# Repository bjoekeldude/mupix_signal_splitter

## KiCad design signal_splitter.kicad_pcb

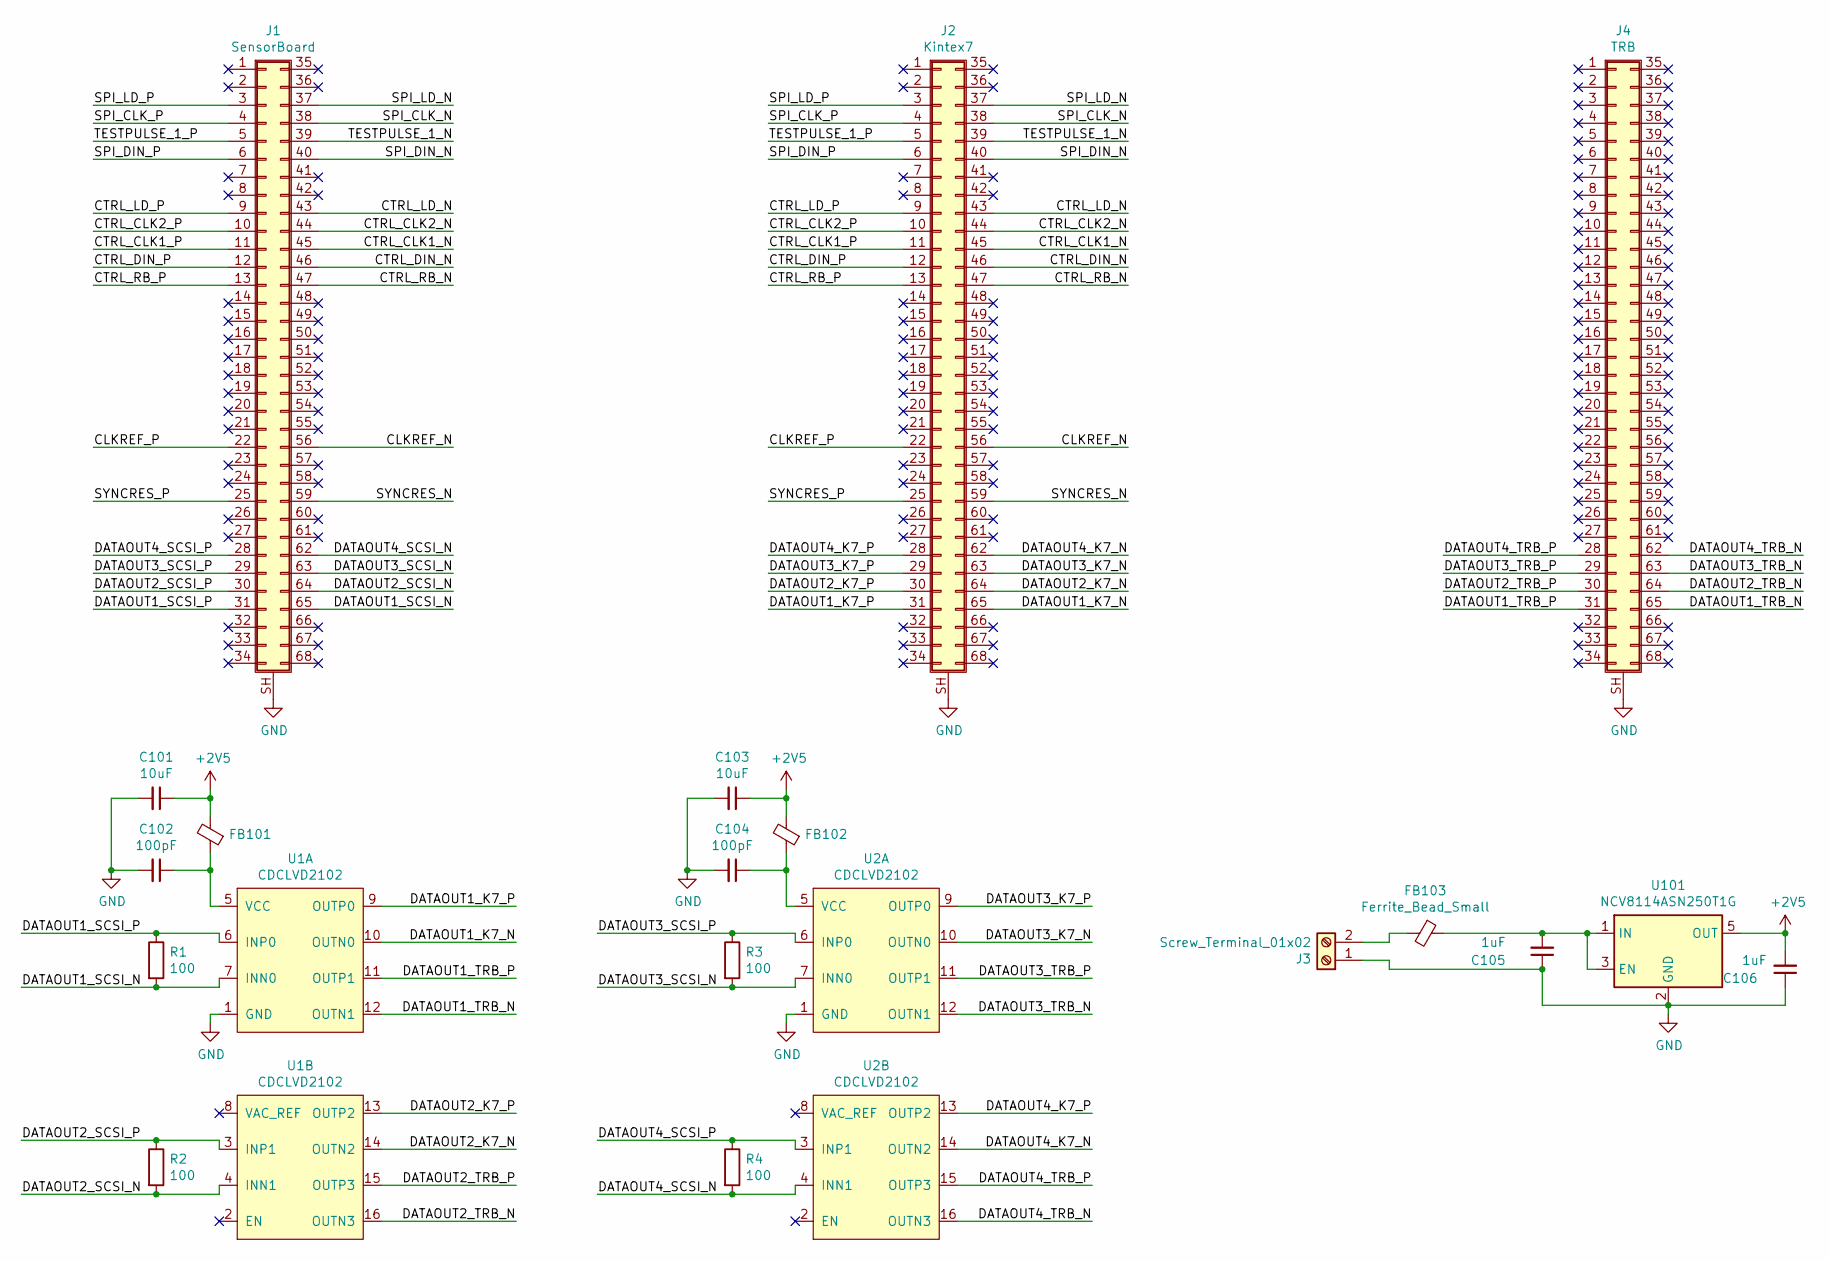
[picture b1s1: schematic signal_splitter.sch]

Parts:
C101, C103: 10uF; C_0402_1005Metric
C102, C104: 100pF; C_0402_1005Metric
C105, C106: 1uF; C_0603_1608Metric
FB101, FB102, FB103: Ferrite_Bead_Small; C_0603_1608Metric
J1: SensorBoard; TE 5749069-7
J2: Kintex7; TE 5749069-7
J3: Screw_Terminal_01x02; TerminalBlock_RND_205-00232_1x02_P5.08mm_Horizontal
J4: TRB; TE 5749069-7
R1, R2, R3, R4: 100; R_0402_1005Metric_Pad0.72x0.64mm_HandSolder
U1, U2: CDCLVD2102; QFN-16-1EP_3x3mm_P0.5mm_EP1.75x1.75mm_ThermalVias; MPN CDCLVD2102RGT
U101: NCV8114ASN250T1G; TSOT-23-5

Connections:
+2V5: C101.1, C103.1, C106.2, FB101.2, FB102.2, U101.5 (OUT)
/CLKREF_N: J1.56, J2.56
/CLKREF_P: J1.22, J2.22
/CTRL_CLK1_N: J1.45, J2.45
/CTRL_CLK1_P: J1.11, J2.11
/CTRL_CLK2_N: J1.44, J2.44
/CTRL_CLK2_P: J1.10, J2.10
/CTRL_DIN_N: J1.46, J2.46
/CTRL_DIN_P: J1.12, J2.12
/CTRL_LD_N: J1.43, J2.43
/CTRL_LD_P: J1.9, J2.9
/CTRL_RB_N: J1.47, J2.47
/CTRL_RB_P: J1.13, J2.13
/DATAOUT1_K7_N: J2.65, U1.10 (OUTN0)
/DATAOUT1_K7_P: J2.31, U1.9 (OUTP0)
/DATAOUT1_SCSI_N: J1.65, R1.2, U1.7 (INN0)
/DATAOUT1_SCSI_P: J1.31, R1.1, U1.6 (INP0)
/DATAOUT1_TRB_N: J4.65, U1.12 (OUTN1)
/DATAOUT1_TRB_P: J4.31, U1.11 (OUTP1)
/DATAOUT2_K7_N: J2.64, U1.14 (OUTN2)
/DATAOUT2_K7_P: J2.30, U1.13 (OUTP2)
/DATAOUT2_SCSI_N: J1.64, R2.2, U1.4 (INN1)
/DATAOUT2_SCSI_P: J1.30, R2.1, U1.3 (INP1)
/DATAOUT2_TRB_N: J4.64, U1.16 (OUTN3)
/DATAOUT2_TRB_P: J4.30, U1.15 (OUTP3)
/DATAOUT3_K7_N: J2.63, U2.10 (OUTN0)
/DATAOUT3_K7_P: J2.29, U2.9 (OUTP0)
/DATAOUT3_SCSI_N: J1.63, R3.2, U2.7 (INN0)
/DATAOUT3_SCSI_P: J1.29, R3.1, U2.6 (INP0)
/DATAOUT3_TRB_N: J4.63, U2.12 (OUTN1)
/DATAOUT3_TRB_P: J4.29, U2.11 (OUTP1)
/DATAOUT4_K7_N: J2.62, U2.14 (OUTN2)
/DATAOUT4_K7_P: J2.28, U2.13 (OUTP2)
/DATAOUT4_SCSI_N: J1.62, R4.2, U2.4 (INN1)
/DATAOUT4_SCSI_P: J1.28, R4.1, U2.3 (INP1)
/DATAOUT4_TRB_N: J4.62, U2.16 (OUTN3)
/DATAOUT4_TRB_P: J4.28, U2.15 (OUTP3)
/SPI_CLK_N: J1.38, J2.38
/SPI_CLK_P: J1.4, J2.4
/SPI_DIN_N: J1.40, J2.40
/SPI_DIN_P: J1.6, J2.6
/SPI_LD_N: J1.37, J2.37
/SPI_LD_P: J1.3, J2.3
/SYNCRES_N: J1.59, J2.59
/SYNCRES_P: J1.25, J2.25
/TESTPULSE_1_N: J1.39, J2.39
/TESTPULSE_1_P: J1.5, J2.5
GND: C101.2, C102.2, C103.2, C104.2, C105.1, C106.1, J1.SH (Shield), J2.SH (Shield), J3.1, J4.SH (Shield), U1.1 (GND), U2.1 (GND), U101.2 (GND)
unnamed: C102.1, FB101.1, U1.5 (VCC)
unnamed: C104.1, FB102.1, U2.5 (VCC)
unnamed: C105.2, FB103.1, U101.1 (IN), U101.3 (EN)
unnamed: FB103.2, J3.2

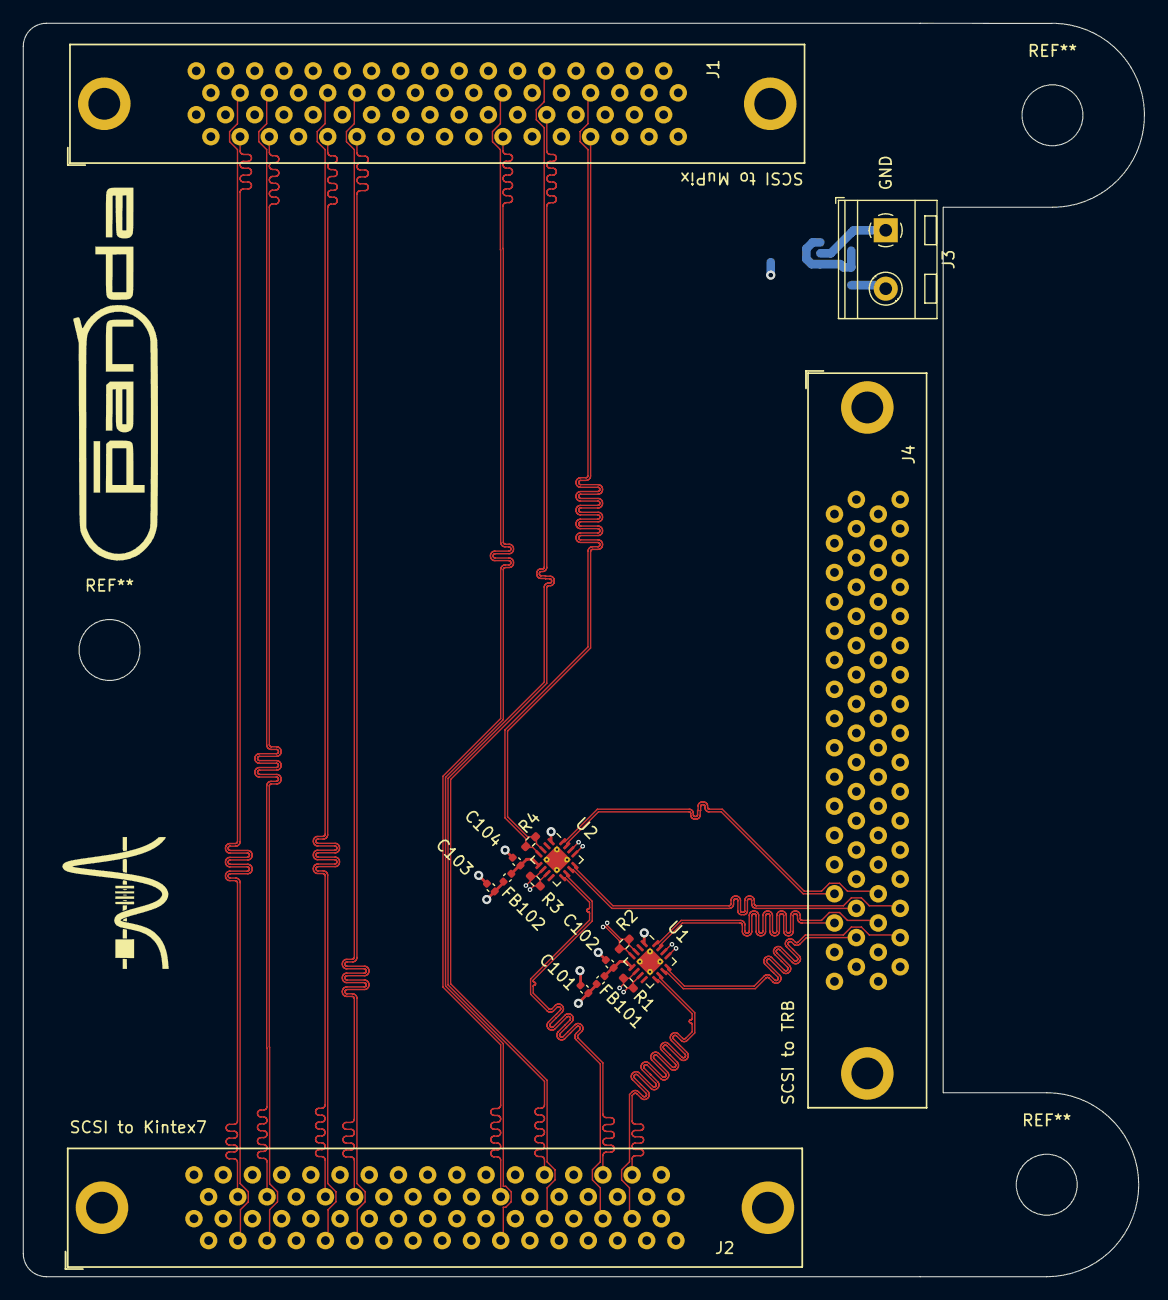
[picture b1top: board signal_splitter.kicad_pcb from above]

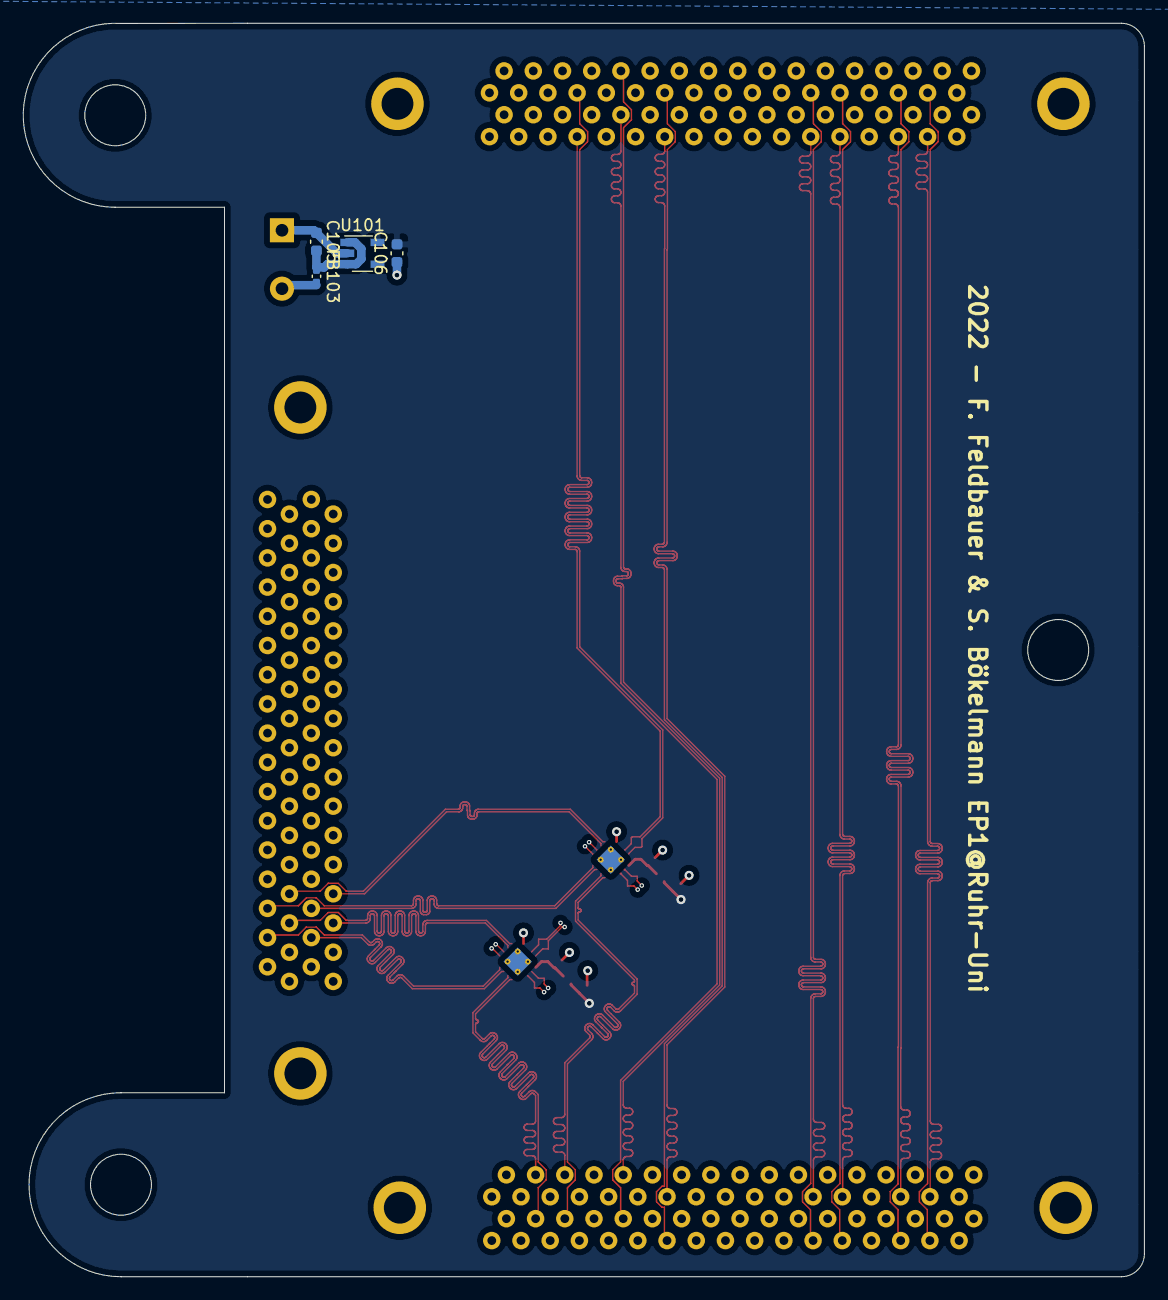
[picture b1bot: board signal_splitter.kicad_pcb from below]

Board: 4 copper layers, 97.5 x 109.0 mm, 20 parts (4 on the bottom side), 52 nets.

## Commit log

2022-03-22 final
